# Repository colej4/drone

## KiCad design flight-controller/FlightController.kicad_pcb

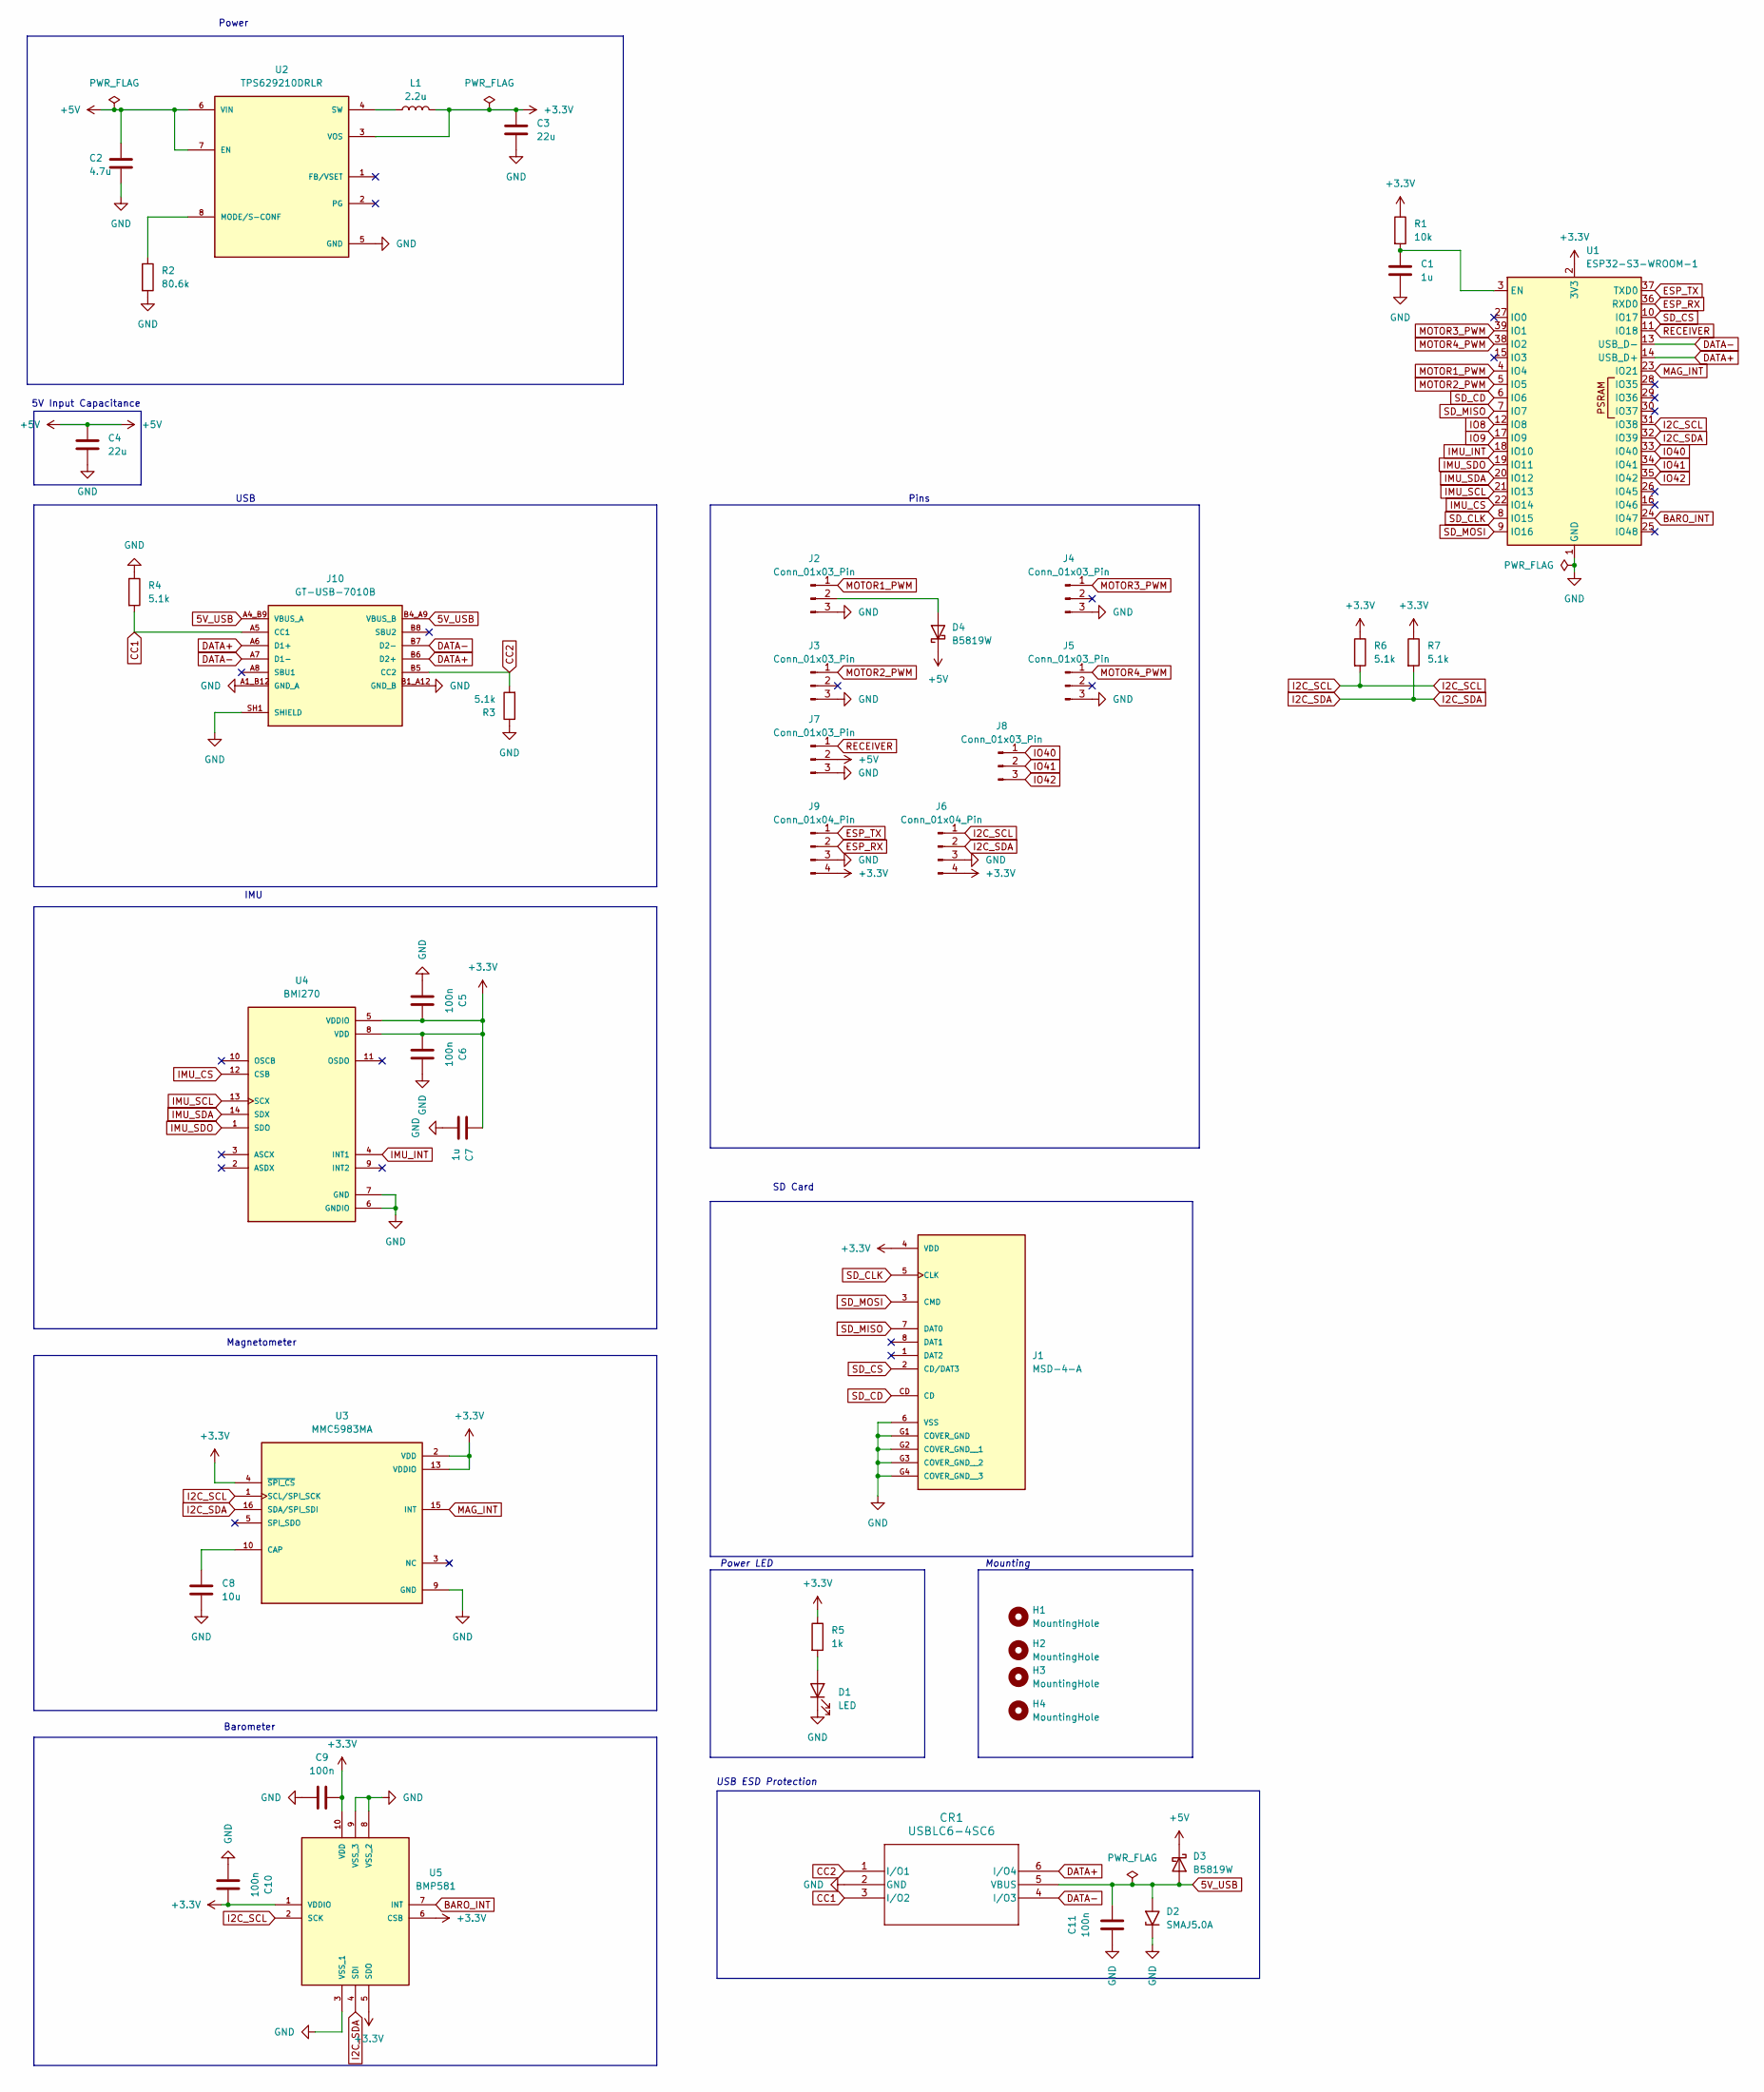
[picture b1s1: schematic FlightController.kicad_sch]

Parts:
C1, C7: 1u; C_0603_1608Metric_Pad1.08x0.95mm_HandSolder
C2: 4.7u; C_0603_1608Metric_Pad1.08x0.95mm_HandSolder
C3, C4: 22u; C_0603_1608Metric_Pad1.08x0.95mm_HandSolder
C5, C6, C9, C10, C11: 100n; C_0603_1608Metric_Pad1.08x0.95mm_HandSolder
C8: 10u; C_0603_1608Metric_Pad1.08x0.95mm_HandSolder
CR1: USBLC6-4SC6; SOT23-6L_STM
D1: LED; LED_0805_2012Metric
D2: SMAJ5.0A; D_SMA
D3, D4: B5819W; D_SOD-123
H1, H2, H3, H4: MountingHole; MountingHole_3.2mm_M3
J1: MSD-4-A; CUI_MSD-4-A; PARTREV 1.0
J2, J3, J4, J5, J7, J8: Conn_01x03_Pin; PinHeader_1x03_P2.54mm_Vertical
J6, J9: Conn_01x04_Pin; PinHeader_1x04_P2.54mm_Vertical
J10: GT-USB-7010B; G-SWITCH_GT-USB-7010B; PARTREV A0
L1: 2.2u; L_1008_2520Metric_Pad1.43x2.20mm_HandSolder
R1: 10k; R_0603_1608Metric_Pad0.98x0.95mm_HandSolder
R2: 80.6k; R_0603_1608Metric_Pad0.98x0.95mm_HandSolder
R3, R4, R6, R7: 5.1k; R_0603_1608Metric_Pad0.98x0.95mm_HandSolder
R5: 1k; R_0603_1608Metric_Pad0.98x0.95mm_HandSolder
U1: ESP32-S3-WROOM-1
U2: TPS629210DRLR; SOT50P160X60-8N; PARTREV B
U3: MMC5983MA; PQFN50P300X300X100-16N; PARTREV A
U4: BMI270; XDCR_BMI270
U5: BMP581; Manufacturer_Part_Number BMP581

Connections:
5V_USB: C11.2, CR1.5 (VBUS), D2.2 (A2), D3.2 (A), J10.A4_B9 (VBUS_A), J10.B4_A9 (VBUS_B)
+3.3V: C3.1, C5.2, C6.1, C7.2, C9.2, C10.2, J1.4 (VDD), J6.4, J9.4, L1.2, R1.1, R5.1, R6.1, R7.1, U1.2 (3V3), U2.3 (VOS), U3.2 (VDD), U3.4 (~SPI_CS), U3.13 (VDDIO), U4.5 (VDDIO), U4.8 (VDD), U5.1 (VDDIO), U5.5 (SDO), U5.6 (CSB), U5.10 (VDD)
+5V: C2.2, C4.1, D3.1 (K), D4.1 (K), J7.2, U2.6 (VIN), U2.7 (EN)
BARO_INT: U1.24 (IO47), U5.7 (INT)
CC1: CR1.3 (I/O2), J10.A5 (CC1), R4.2
CC2: CR1.1 (I/O1), J10.B5 (CC2), R3.2
DATA+: CR1.6 (I/O4), J10.A6 (D1+), J10.B6 (D2+), U1.14 (USB_D+)
DATA-: CR1.4 (I/O3), J10.A7 (D1-), J10.B7 (D2-), U1.13 (USB_D-)
ESP_RX: J9.2, U1.36 (RXD0)
ESP_TX: J9.1, U1.37 (TXD0)
GND: C1.2, C2.1, C3.2, C4.2, C5.1, C6.2, C7.1, C8.2, C9.1, C10.1, C11.1, CR1.2 (GND), D1.1 (K), D2.1 (A1), J1.6 (VSS), J1.G1 (COVER_GND), J1.G2 (COVER_GND__1), J1.G3 (COVER_GND__2), J1.G4 (COVER_GND__3), J2.3, J3.3, J4.3, J5.3, J6.3, J7.3, J9.3, J10.A1_B12 (GND_A), J10.B1_A12 (GND_B), J10.SH1 (SHIELD), J10.SH2 (SHIELD), J10.SH3 (SHIELD), J10.SH4 (SHIELD), R2.2, R3.1, R4.1, U1.1 (GND), U1.40 (GND), U1.41 (GND), U2.5 (GND), U3.9 (GND), U3.11 (GND), U4.6 (GNDIO), U4.7 (GND), U5.3 (VSS_1), U5.8 (VSS_2), U5.9 (VSS_3)
I2C_SCL: J6.1, R6.2, U1.31 (IO38), U3.1 (SCL/SPI_SCK), U5.2 (SCK)
I2C_SDA: J6.2, R7.2, U1.32 (IO39), U3.16 (SDA/SPI_SDI), U5.4 (SDI)
IMU_CS: U1.22 (IO14), U4.12 (CSB)
IMU_INT: U1.18 (IO10), U4.4 (INT1)
IMU_SCL: U1.21 (IO13), U4.13 (SCX)
IMU_SDA: U1.20 (IO12), U4.14 (SDX)
IMU_SDO: U1.19 (IO11), U4.1 (SDO)
IO8: U1.12 (IO8)
IO9: U1.17 (IO9)
IO40: J8.1, U1.33 (IO40)
IO41: J8.2, U1.34 (IO41)
IO42: J8.3, U1.35 (IO42)
MAG_INT: U1.23 (IO21), U3.15 (INT)
MOTOR1_PWM: J2.1, U1.4 (IO4)
MOTOR2_PWM: J3.1, U1.5 (IO5)
MOTOR3_PWM: J4.1, U1.39 (IO1)
MOTOR4_PWM: J5.1, U1.38 (IO2)
unnamed: D1.2 (A), R5.2
unnamed: D4.2 (A), J2.2
unnamed: C1.1, R1.2, U1.3 (EN)
unnamed: R2.1, U2.8 (MODE/S-CONF)
unnamed: L1.1, U2.4 (SW)
unnamed: C8.1, U3.10 (CAP)
RECEIVER: J7.1, U1.11 (IO18)
SD_CD: J1.CD, U1.6 (IO6)
SD_CLK: J1.5 (CLK), U1.8 (IO15)
SD_CS: J1.2 (CD/DAT3), U1.10 (IO17)
SD_MISO: J1.7 (DAT0), U1.7 (IO7)
SD_MOSI: J1.3 (CMD), U1.9 (IO16)

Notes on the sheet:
Magnetometer
Mounting
5V Input Capacitance
Pins
USB ESD Protection
SD Card
Barometer
Power LED
USB
IMU
Power

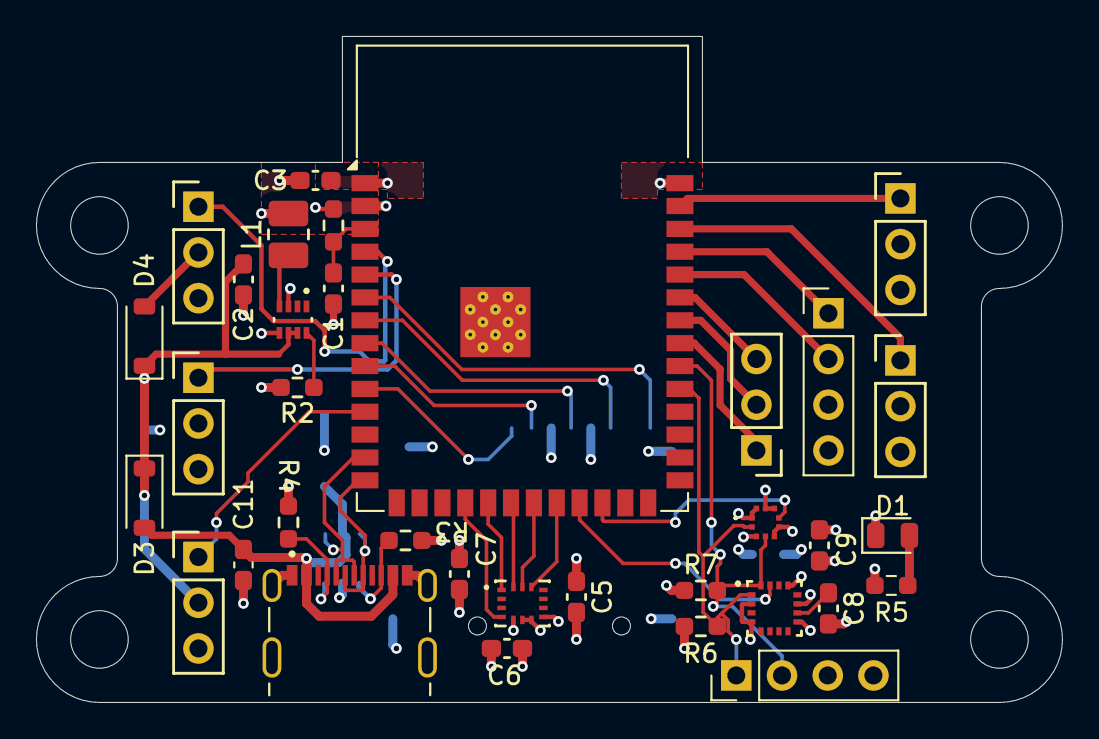
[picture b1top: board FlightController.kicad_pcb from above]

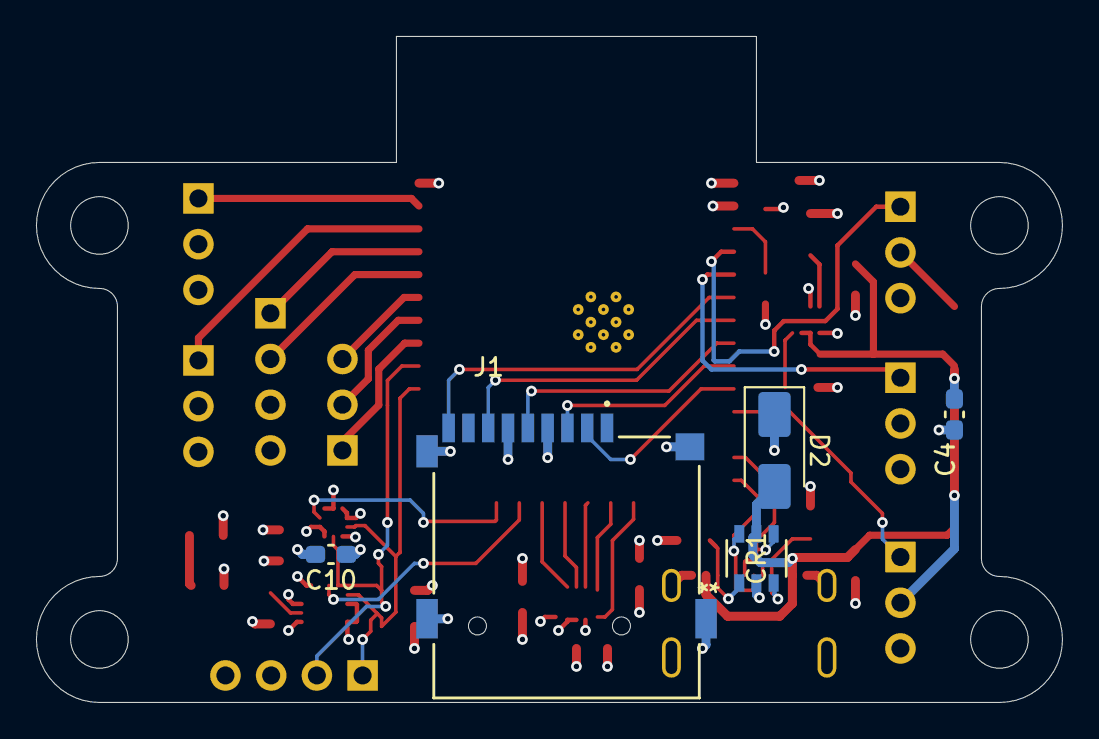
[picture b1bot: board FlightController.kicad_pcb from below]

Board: 4 copper layers, 57.0 x 37.0 mm, 43 parts (5 on the bottom side), 38 nets.

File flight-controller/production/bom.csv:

Designator,Footprint,Quantity,Value,LCSC Part #
"C1, C7",0603,2,1u,
"C10, C11, C5, C6, C9",0603,5,100n,
C2,0603,1,4.7u,
"C3, C4",0603,2,22u,
C8,0603,1,10u,
CR1,SOT23-6L_STM,1,USBLC6-4SC6,
D1,0805,1,LED,
D2,D_SMA,1,SMAJ5.0A,
"D3, D4",D_SOD-123,2,B5819W,
J1,CUI_MSD-4-A,1,MSD-4-A,
J10,G-SWITCH_GT-USB-7010B,1,GT-USB-7010B,
"J2, J3, J4, J5, J7, J8",PinHeader_1x03_P2.54mm_Vertical,6,Conn_01x03_Pin,
"J6, J9",PinHeader_1x04_P2.54mm_Vertical,2,Conn_01x04_Pin,
L1,1008,1,2.2u,
R1,0603,1,10k,
R2,0603,1,80.6k,
"R3, R4, R6, R7",0603,2,5.1k,
R5,0603,1,1k,
U1,ESP32-S3-WROOM-1,1,ESP32-S3-WROOM-1,
U2,SOT50P160X60-8N,1,TPS629210DRLR,
U3,PQFN50P300X300X100-16N,1,MMC5983MA,
U4,XDCR_BMI270,1,BMI270,
U5,BMP581,1,BMP581,

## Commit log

2025-11-17 initial commit, IBUS logic
2025-11-17 Simulink model used to develop control system
2025-11-24 draft of pid controller + task
2025-11-24 draft of some FF controllers
2025-11-24 some code for using joystick to find desired force/quat
2025-11-27 imu code + some joystick stuff
2025-12-04 imu bias and calibration
2025-12-04 state estimation and control
2025-12-04 fix main task
2025-12-04 guard all header files
2026-01-19 many updates, first flight test code
2026-01-19 fix recovery for IBUS packet header
2026-01-19 emergency stop
2026-02-01 modify some params for new props after flight test
2026-02-01 switch printing to use esp_log
2026-02-01 add wifi logging
2026-02-01 compiles in cpp
2026-02-02 add eigen as component
2026-02-03 sd card draft
2026-02-04 functional sd logging
2026-02-04 ekf code compiles, needds testing
2026-02-04 cascading P and PID loop in matlab
2026-02-07 cascading pid, tuning and logging changes
2026-02-07 timeout for loss of controller input
2026-02-08 initialize controller input to 0 to ensure proper behvaior when controller disconnected.
2026-02-27 Update matlab model to reflect better prop model and retune params
2026-02-27 interrupt based imu for proper 1khz polling
2026-03-05 More tuning and math
2026-03-05 pd tuning in matlab
2026-03-05 center of mass (WIP)
2026-03-05 tune integral
2026-03-05 increase gains, fix eigen
2026-03-05 ekf draft updates
2026-03-06 ekf (needs testing)
2026-03-06 matlab changes
2026-03-06 more gain tuning
2026-03-06 use ekf orientation
2026-03-19 5V -> 3.3V DC-DC
2026-03-20 switch to new esp with native usb
2026-03-21 Add a bunch of sensors
2026-03-25 schematic should be done
2026-03-25 update usb
2026-03-25 add footprints
2026-03-25 general component locations
2026-03-25 DRC no errors
2026-03-26 first draft with layout
2026-03-26 add uart header
2026-03-26 add mounting holes
2026-03-27 esd protection
2026-03-27 switch usb port, add schottky diode
2026-03-29 design files
2026-03-29 4 layerify board
